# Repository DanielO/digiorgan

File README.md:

Carrier board for a Teensy 3.5 to control 32 servos.

Designed to play music in a Castlewood Busker Organ.

It only has 20 notes but we are using 2x16 PWM controllers so it may be of use for
other organs.

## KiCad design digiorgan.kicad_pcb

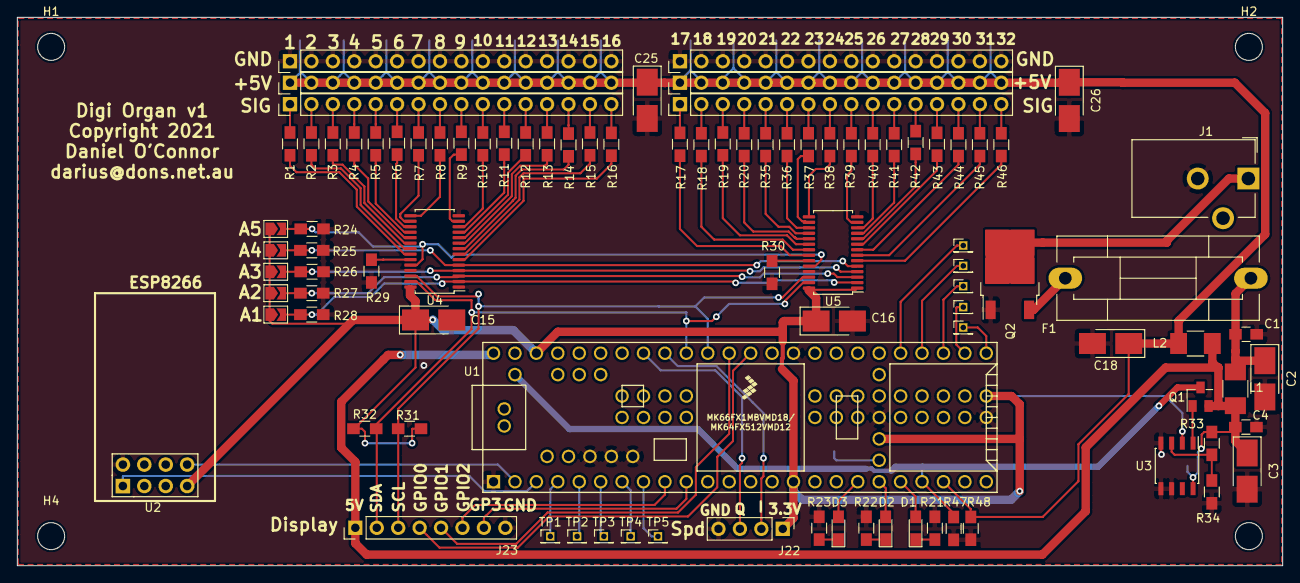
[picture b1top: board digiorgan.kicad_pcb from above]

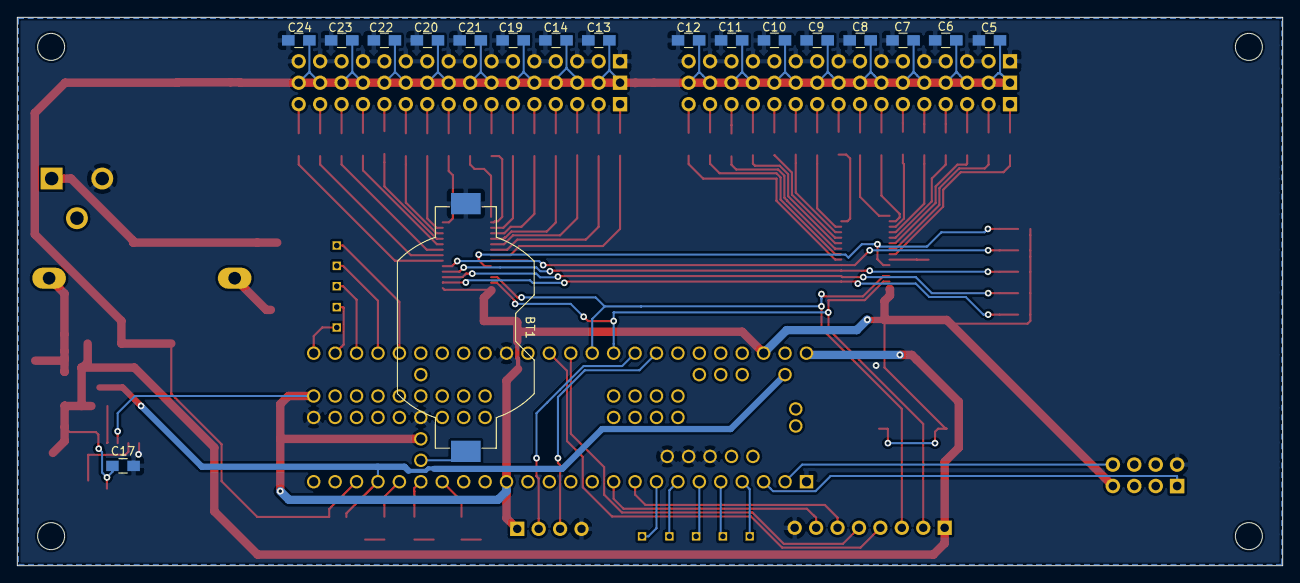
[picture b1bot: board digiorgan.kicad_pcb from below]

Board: 2 copper layers, 150.0 x 65.0 mm, 116 parts (18 on the bottom side), 108 nets.

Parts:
BT1: Battery_Cell; Keystone_1058_1x2032-CoinCell
C1, C4, C5, C6, C7, C8, C9, C10, C11, C12, C13, C14, C17, C19, C20, C21, C22, C23, C24: 100n; C_0805_HandSoldering
C2, C3, C15, C16, C18, C25, C26: 10uF 25V; CP_Tantalum_Case-B_EIA-3528-21_Hand
D1, D2, D3: LED; LED_0805_HandSoldering
F1: Fuse; Fuseholder5x20_horiz_SemiClosed_Casing10x25mm
H1, H2, H3, H4: MountingHole; MountingHole_3.2mm_M3
J1: Barrel_Jack_Switch; Barrel_Jack_CUI_PJ-102AH
J2, J5: Conn_01_16_Male; Pin_Header_Straight_1x16_Pitch2.54mm
J3, J4, J6, J7: Conn_01x16_Male; Pin_Header_Straight_1x16_Pitch2.54mm
J22: Conn_01x04_MountingPin; Pin_Header_Straight_1x04_Pitch2.54mm
J23: Conn_01x08_MountingPin; Pin_Header_Straight_1x08_Pitch2.54mm
JP1, JP2, JP3, JP4, JP5: SolderJumper_2_Open; SolderJumper-2_P1.3mm_Open_TrianglePad1.0x1.5mm
L1, L2: INDUCTOR; L_1210_HandSoldering
Q1: FDN304P; SuperSOT-3
Q2: AOD417; TO-252-2
R1, R2, R3, R4, R5, R6, R7, R8, R9, R10, R11, R12, R13, R14, R15, R16, R17, R18, R19, R20, R35, R36, R37, R38, R39, R40, R41, R42, R43, R44, R45, R46: 100; R_0805_HandSoldering
R21, R22, R23: 1k; R_0805_HandSoldering
R24, R25, R26, R27, R28, R29, R30, R33, R34: 10k; R_0805_HandSoldering
R31, R32: 4k7; R_0805_HandSoldering
R47, R48: 50k; R_0805_HandSoldering
TP1, TP2, TP3, TP4, TP5, TP6, TP7, TP8, TP9, TP10: TestPoint; Pin_Header_Straight_1x01_Pitch1.27mm
U1: Teensy3.5; Teensy35_36_All_Pins
U2: ESP-01v090; ESP-01
U3: LM358; SOIC-8_3.9x4.9mm_Pitch1.27mm
U4, U5: PCA9685PW; TSSOP-28_4.4x9.7mm_P0.65mm

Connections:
+3V3: C15.1, C16.1, J22.1, JP1.1, JP2.1, JP3.1, JP4.1, JP5.1, R31.1, R32.1, U1.15, U1.26, U1.51, U1.75, U2.7, U3.2, U4.28, U5.1, U5.28
+5V: C3.1, C4.1, C17.1, J23.1, L1.2, L2.1, Q1.2, R33.1, U1.53, U3.8
/DISP_GPIO0: J23.4, U1.41
/DISP_GPIO1: J23.5, U1.42
/DISP_GPIO2: J23.6, U1.9
/DISP_GPIO3: J23.7, U1.10
/ESP_RX: U1.2, U2.8
/ESP_TX: U1.3, U2.1
/I2C_SCL: J23.3, R31.2, U1.43, U4.26, U5.26
/I2C_SDA: J23.2, R32.2, U1.44, U4.27, U5.27
/SERVO_0: R1.2, U4.22
/SERVO_1: R2.2, U4.21
/SERVO_2: R3.2, U4.20
/SERVO_3: R4.2, U4.19
/SERVO_4: R5.2, U4.18
/SERVO_5: R6.2, U4.17
/SERVO_6: R7.2, U4.16
/SERVO_7: R8.2, U4.15
/SERVO_8: R9.2, U4.13
/SERVO_9: R10.2, U4.12
/SERVO_10: R11.2, U4.11
/SERVO_11: R12.2, U4.10
/SERVO_12: R13.2, U4.9
/SERVO_13: R14.2, U4.8
/SERVO_14: R15.2, U4.7
/SERVO_15: R16.2, U4.6
/SERVO_16: R17.2, U5.22
/SERVO_17: R18.2, U5.21
/SERVO_18: R19.2, U5.20
/SERVO_19: R20.2, U5.19
/SERVO_20: R35.2, U5.18
/SERVO_21: R36.2, U5.17
/SERVO_22: R37.2, U5.16
/SERVO_23: R38.2, U5.15
/SERVO_24: R39.2, U5.13
/SERVO_25: R40.2, U5.12
/SERVO_26: R41.2, U5.11
/SERVO_27: R42.2, U5.10
/SERVO_28: R43.2, U5.9
/SERVO_29: R44.2, U5.8
/SERVO_31: R45.2, U5.7
/SERVO_32: R46.2, U5.6
/SPEED_SENSE_I: J22.2, U1.45
/SPEED_SENSE_Q: J22.3, U1.46
GND: BT1.2, C1.2, C2.2, C3.2, C4.2, C5.2, C6.2, C7.2, C8.2, C9.2, C10.2, C11.2, C12.2, C13.2, C14.2, C15.2, C16.2, C17.2, C18.2, C19.2, C20.2, C21.2, C22.2, C23.2, C24.2, C25.2, C26.2, J1.2, J4.1, J4.2, J4.3, J4.4, J4.5, J4.6, J4.7, J4.8, J4.9, J4.10, J4.11, J4.12, J4.13, J4.14, J4.15, J4.16, J7.1, J7.2, J7.3, J7.4, J7.5, J7.6, J7.7, J7.8, J7.9, J7.10, J7.11, J7.12, J7.13, J7.14, J7.15, J7.16, J22.4, J23.8, Q2.1, R21.1, R22.2, R23.1, R24.2, R25.2, R26.2, R27.2, R28.2, R29.2, R30.2, R34.2, R47.2, R48.2, U1.1, U1.27, U1.39, U1.60, U1.61, U1.62, U1.74, U2.2, U3.4, U3.5, U3.6, U4.1, U4.14, U4.25, U5.14, U5.25
unnamed: BT1.1, U1.25
unnamed: C1.1, C2.1, F1.1, L1.1
unnamed: D1.1, R21.2
unnamed: D1.2, U1.20
unnamed: D2.1, R22.1
unnamed: D2.2, U1.19
unnamed: D3.1, R23.2
unnamed: D3.2, U1.18
unnamed: F1.2, Q2.3
unnamed: J1.1, Q2.2
unnamed: J2.1, R1.1
unnamed: J2.2, R2.1
unnamed: J2.3, R3.1
unnamed: J2.4, R4.1
unnamed: J2.5, R5.1
unnamed: J2.6, R6.1
unnamed: J2.7, R7.1
unnamed: J2.8, R8.1
unnamed: J2.9, R9.1
unnamed: J2.10, R10.1
unnamed: J2.11, R11.1
unnamed: J2.12, R12.1
unnamed: J2.13, R13.1
unnamed: J2.14, R14.1
unnamed: J2.15, R15.1
unnamed: J2.16, R16.1
unnamed: J5.1, R17.1
unnamed: J5.2, R18.1
unnamed: J5.3, R19.1
unnamed: J5.4, R20.1
unnamed: J5.5, R35.1
unnamed: J5.6, R36.1
unnamed: J5.7, R37.1
unnamed: J5.8, R38.1
unnamed: J5.9, R39.1
unnamed: J5.10, R40.1
unnamed: J5.11, R41.1
unnamed: J5.12, R42.1
unnamed: J5.13, R43.1
unnamed: J5.14, R44.1
unnamed: J5.15, R45.1
unnamed: J5.16, R46.1
unnamed: JP1.2, R28.1, U4.2, U5.2
unnamed: JP2.2, R27.1, U4.3, U5.3
unnamed: JP3.2, R26.1, U4.4, U5.4
unnamed: JP4.2, R25.1, U4.5, U5.5
unnamed: JP5.2, R24.1, U4.24, U5.24
unnamed: Q1.1, U3.1
unnamed: R29.1, U4.23
unnamed: R30.1, U5.23
unnamed: R33.2, R34.1, U3.3
unnamed: TP1.1, U1.4
unnamed: TP2.1, U1.5
unnamed: TP3.1, U1.6
unnamed: TP4.1, U1.7
unnamed: TP5.1, U1.8
unnamed: TP6.1, U1.30
unnamed: TP7.1, U1.31
unnamed: TP8.1, U1.32
unnamed: TP9.1, U1.33
unnamed: TP10.1, U1.34
VBUS: Q1.3, R47.1, U1.21, U1.54
VPP: C5.1, C6.1, C7.1, C8.1, C9.1, C10.1, C11.1, C12.1, C13.1, C14.1, C18.1, C19.1, C20.1, C21.1, C22.1, C23.1, C24.1, C25.1, C26.1, J3.1, J3.2, J3.3, J3.4, J3.5, J3.6, J3.7, J3.8, J3.9, J3.10, J3.11, J3.12, J3.13, J3.14, J3.15, J3.16, J6.1, J6.2, J6.3, J6.4, J6.5, J6.6, J6.7, J6.8, J6.9, J6.10, J6.11, J6.12, J6.13, J6.14, J6.15, J6.16, L2.2, R48.1, U1.22

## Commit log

2021-09-18 Add submodules
2021-09-18 Add README
2021-09-19 Fix tag footprints. Add test points. Add schematic and PCB PDFs

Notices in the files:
digiorgan.kicad_pcb:
Copyright 2021
